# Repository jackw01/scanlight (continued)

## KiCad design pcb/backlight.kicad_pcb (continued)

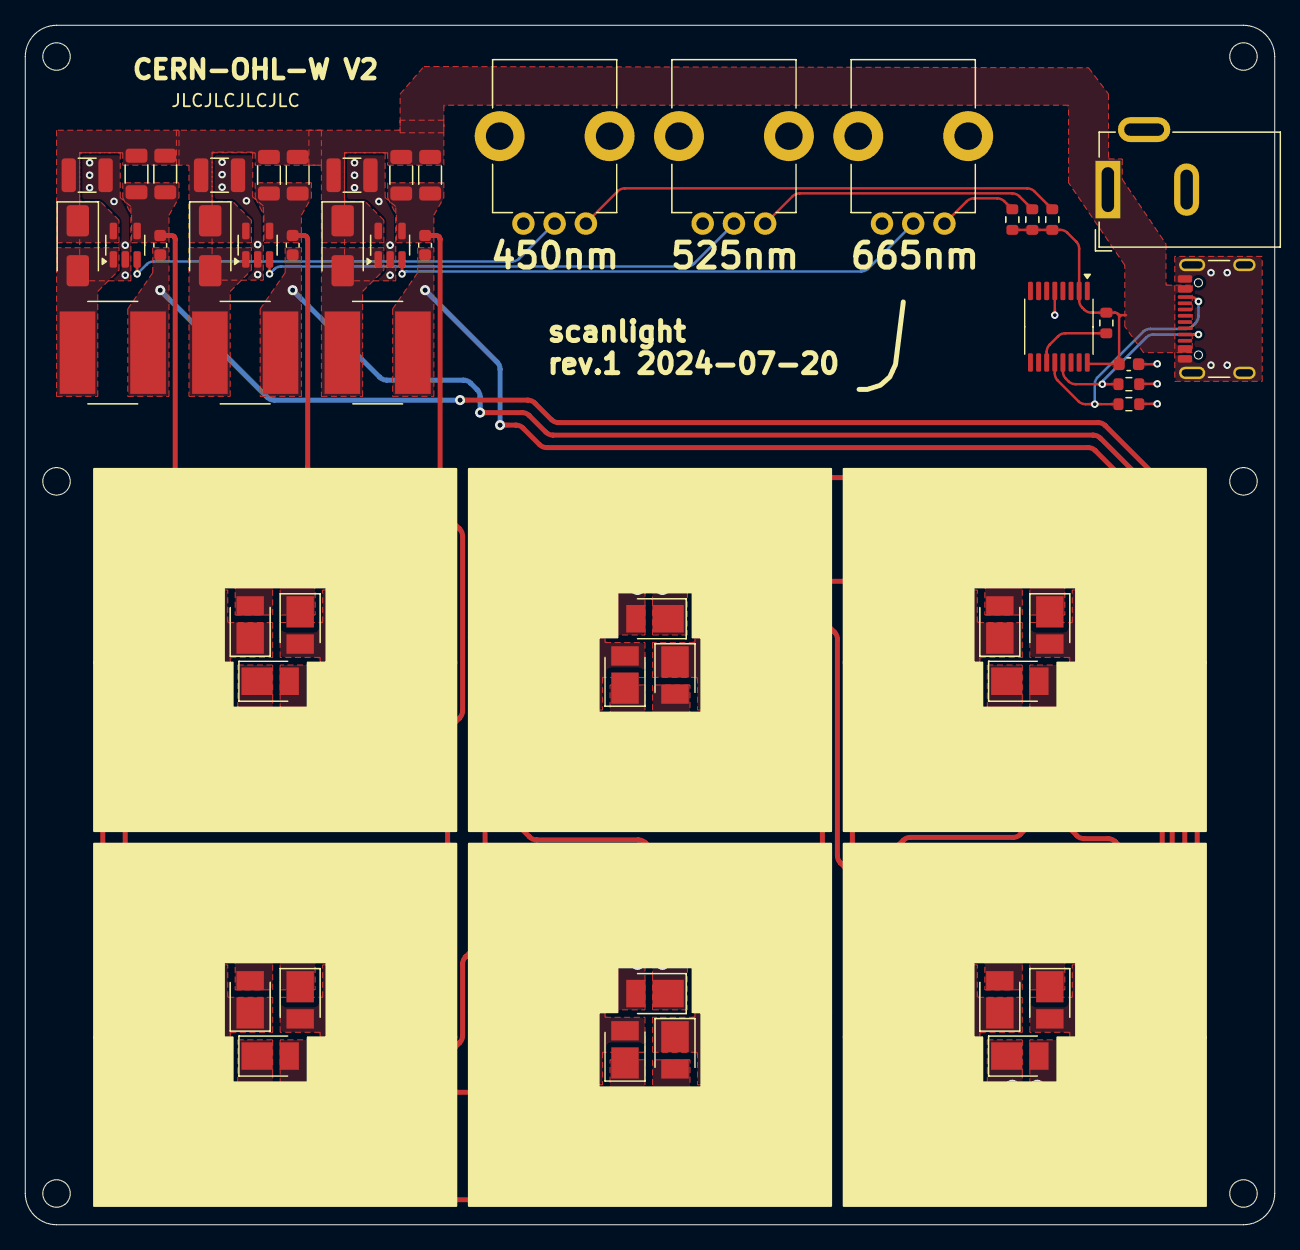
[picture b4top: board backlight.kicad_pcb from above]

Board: 2 copper layers, 100.0 x 96.0 mm, 59 parts (1 on the bottom side), 35 nets.

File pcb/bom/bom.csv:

Reference,Value,Footprint,Qty,DNP,MPN
"C1,C3,C6",10u,Capacitor_SMD:C_1210_3225Metric,3,,Generic 10uF 50V 1210 X7R
"C2,C4,C5,C7",1u,Capacitor_SMD:C_0603_1608Metric,4,,Generic 1uF 25V 0603 X7R
"D1,D2,D3,D4,D5,D6",deep blue,LED_SMD:LED_PLCC_2835_Handsoldering,6,,JE2835ARY-N-0002A0000-N0000001
"D7,D8,D15",B240A,Diode_SMD:D_SMA,3,,B240A-13-F
"D9,D10,D11,D12,D13,D14",green,LED_SMD:LED_PLCC_2835_Handsoldering,6,,JE2835AGR-N-0002A0000-N0000001
"D16,D17,D18,D19,D20,D21",deep red,LED_SMD:LED_PLCC_2835_Handsoldering,6,,67-21S/NDR3C-P5080C1C51827Z15/2T
"H1,H2,H3,H4,H5,H6",MountingHole,Custom:MountingHole_2.2mm_M2_Mask_5mm,6,,
J3,PJ-002B,Connector_BarrelJack:BarrelJack_GCT_DCJ200-10-A_Horizontal,1,,PJ-002B
J6,USB_C_Receptacle_USB2.0,Connector_USB:USB_C_Receptacle_GCT_USB4105-xx-A_16P_TopMnt_Horizontal,1,,USB4105-GF-A
"L1,L2,L3",100u,Inductor_SMD:L_Bourns_SRN8040TA,3,,HPC 8040NV-101M 
"R1,R4,R9,R10,R11,R12",1.4,Resistor_SMD:R_1206_3216Metric,6,,RK73H2ATTD1R40F
"R2,R3,R5",649k,Resistor_SMD:R_0603_1608Metric,3,,Generic 649KOhm 0603 1%
R6,100k,Resistor_SMD:R_0603_1608Metric,1,,Generic 100KOhm 0603 5%
"R7,R8",5.1k,Resistor_SMD:R_0603_1608Metric,2,,Generic 5.1KOhm 0603 5%
"RV1,RV2,RV3",100k,Potentiometer_THT:Potentiometer_Bourns_PTV09A-1_Single_Vertical,3,,PTV09A-4020U-B104
SYM101,SYM_Hot_Large,Custom:hot-surface_1x,1,,
"U1,U3,U4",AL8860WT,Package_TO_SOT_SMD:TSOT-23-5,3,,AL8860WT-7
U2,IP2721,Package_SO:TSSOP-16_4.4x5mm_P0.65mm,1,,IP2721

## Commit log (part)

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2024-08-03 testing
2024-08-03 add pcb
2024-08-03 add 3d files
2024-10-09 fix incorrect part number in BOM
2025-01-13 test gh pages publish
2025-07-02 add rev2 pcb
2025-07-19 luminance plots
2025-07-20 update hw_v2
2025-07-20 add new shop link
2025-07-20 link v2 page
2025-07-20 add parts list
2025-08-02 add upgrade instructions
2025-08-02 minor updates to 3d files
2025-08-13 control app
2025-08-13 favicon
2025-08-15 add horizontal mount cad
2025-08-21 slightly improved 35mm mask design + half frame mask
2025-11-09 current production firmware
2025-11-30 separate firmware/app for sl3 and bsl1
2025-11-30 big scanlight app test build
2025-12-01 add svg diagrams
2025-12-02 update docs
2025-12-08 big scanlight info page
2025-12-11 test new siteconfig/images
2025-12-16 big scanlight firmware and app
2025-12-16 big scanlight website/app build
2025-12-16 pcb files
2025-12-18 add v3 snapfit design files
2025-12-26 add big scanlight assembly instructions
2025-12-26 fix markdown headings
2025-12-28 big scanlight step files
2025-12-28 add assembly step file
2025-12-28 fix github links
2025-12-31 add tonecarrier adapter
2026-01-14 add valoi360 adapter info
2026-02-12 firmware interface documentation
2026-05-03 update bsl firmware and app for v4 compatibility
2026-05-08 reorganize cad files, add latest big scanlight changes
2026-05-09 scanlight v4 page
2026-05-09 update drawings and v4 page
2026-05-09 publish v4 CAD
2026-05-10 v4 firmware and flashing script
2026-05-12 add adapter note
2026-05-28 add debug messages to webapp
2026-06-05 add v4 horizontal mount option CAD
2026-06-06 update v4 tonecarrier plate
2026-06-21 improved valoi 360 adapter files
2026-06-28 add pre-shutter delay and keep light on option to web app
